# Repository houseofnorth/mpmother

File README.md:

# MPMOTHER

House of North 2026

| Knob | Name     | MIDI Out (default) | MIDI In (default) |
|------|----------|--------------------|-------------------|
| 1    | SPACE    | ch 1, CC 20        | ch 2, CC 20       |
| 2    | TEXTURE  | ch 1, CC 21        | ch 2, CC 21       |
| 3    | MOVEMENT | ch 1, CC 22        | ch 2, CC 22       |
| 4    | SHADOW   | ch 1, CC 23        | ch 2, CC 23       |

MIDI Out is what a knob sends, MIDI In is what moves it. Every knob has its own channel and CC
for both, set in the config tool.

## Using it with Ableton Live

- **Map a knob:** MIDI-map a parameter to the knob as usual.
- **Knobs follow the set:** in Live's MIDI preferences, turn on *Remote* for the MPMOTHER
  **output**. Live then sends mapping feedback and the knobs jump to the right place.
- **Let Ableton drive the knobs:** send ch 2, CC 20–23 to MPMOTHER from a MIDI track
  (clips, automation, Max for Live LFOs). The knobs move and send their position, so whatever
  is mapped to them follows.
- A hand on a knob always wins.
- **Without motors:** Settings → *Motors* Off makes MPMOTHER a plain controller: the knobs only
  send, MIDI In is ignored.

## Config tool

Open <https://houseofnorth.github.io/mpmother/> in Chrome or Edge with the controller plugged in.
The first time, Chrome asks for permission to use MIDI devices: click **Allow**, the page needs it.
The main page shows the four knobs live (position, where the motor is heading, hand on knob).
**Settings** (top right) has all settings, calibration, wiper readings and faults.
It works while Ableton is running.

**As an app, offline:** click **Install** (top right; or the install icon in Chrome's address bar).
MPMOTHER then opens in its own window from the Dock / Start menu and works without internet.
It updates itself whenever it is opened online.

**Demo** (top right): with the controller connected, the knobs make random moves until you
press Demo again. Without a controller it shows a simulated one.

## Status LED

| Colour          | Meaning |
|-----------------|---------|
| dim green       | ready |
| blue flicker    | MIDI in or out |
| red blink       | fault, motors held off |
| solid red       | driver kept faulting, needs *Clear faults* or a power cycle |
| white blink ×3  | restarted by the watchdog |

## Hardware

A main board (MPMOTHER v1) and one pot board (MPCHILD v1) per knob. Schematic, board file,
Gerbers and pictures: [hardware/](hardware/).

## Firmware

PlatformIO project. Open this folder in VS Code with the PlatformIO extension, then
*Build* (✓) and *Upload* (→). Serial monitor at 115200 – type `help` for text commands.

First time on new hardware: run **Calibrate** (config tool or `calibrate`), hands off the knobs.

Code layout and tuning values are explained at the top of each file in `src/`.
SysEx details: [PROTOCOL.md](PROTOCOL.md).

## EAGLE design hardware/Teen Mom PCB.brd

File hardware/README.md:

# Hardware

Schematics and board files for MPMOTHER v1, designed in Fusion Electronics.

| Board | What it is |
|-------|------------|
| MPMOTHER v1 | Main board: Teensy 4.1, two Pololu DRV8833 drivers, four IDC 2×4 headers to the pot boards |
| MPCHILD v1  | Pot board, one per knob: the motorised pot and its IDC 2×4 header |

## Files

| File | What it is |
|------|------------|
| [`Teensy_Mother_Schematic.sch`](Teensy_Mother_Schematic.sch) | MPMOTHER v1 schematic (EAGLE format, from Fusion Electronics) |
| [`Teen Mom PCB.brd`](Teen%20Mom%20PCB.brd) | MPMOTHER v1 board layout (EAGLE format, "Teen Mom PCB" in Fusion) |
| [`gerbers/Teen_Mom_PCB_Manufacturing_Output.zip`](gerbers/Teen_Mom_PCB_Manufacturing_Output.zip) | MPMOTHER v1 manufacturing output: Gerbers, drill, pick and place, parts list |
| [`gerbers/Motorboard_pcb_Manufacturing_Output.zip`](gerbers/Motorboard_pcb_Manufacturing_Output.zip) | MPCHILD v1 manufacturing output: Gerbers, drill, pick and place |

The Gerber zips are the v1 boards as ordered (JLCPCB): upload a zip as it is.
Pin map and wiring as used by the firmware: [`src/pins.h`](../src/pins.h).

## MPMOTHER v1 (main board)

Layout:

Schematic:

## MPCHILD v1 (pot board)

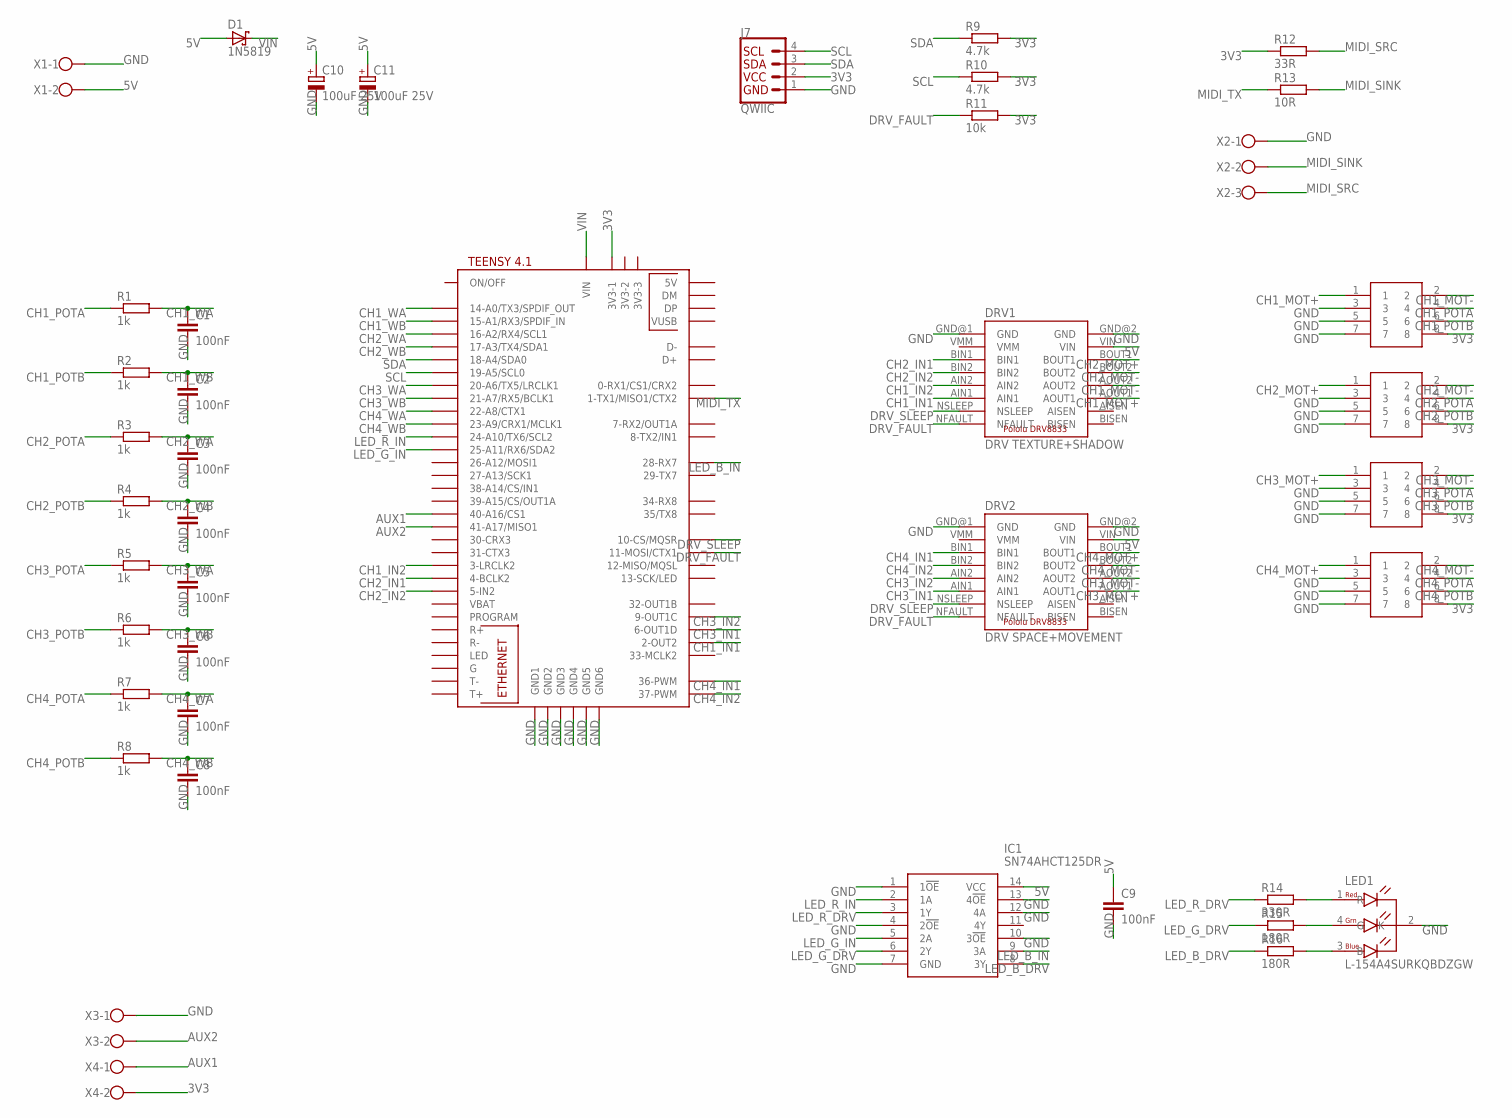
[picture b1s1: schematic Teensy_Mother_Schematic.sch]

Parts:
C1, C2, C3, C4, C5, C6, C7, C8, C9: 100nF; C050-025X075
C10, C11: 100uF 25V; E3,5-8
D1: 1N5819; DO41-10
DRV1: DRV TEXTURE+SHADOW; POLOLU_2130_FH
DRV2: DRV SPACE+MOVEMENT; POLOLU_2130_FH
IC1: SN74AHCT125DR; SOIC127P600X175-14N
J1: SHADOW; BOXHDR_2X4_V
J2: TEXTURE; BOXHDR_2X4_V
J3: MOVEMENT; BOXHDR_2X4_V
J4: SPACE; BOXHDR_2X4_V
J7: QWIIC; 1X04
LED1: L-154A4SURKQBDZGW; LED5MM_RGB_4L_STAGGER
R1, R2, R3, R4, R5, R6, R7, R8: 1k; 0204/7
R9, R10: 4.7k; 0204/7
R11: 10k; 0204/7
R12: 33R; 0204/7
R13: 10R; 0204/7
R14: 330R; 0204/7
R15, R16: 180R; 0204/7
U$1: TEENSY41
X1, X3, X4: W237-1023D; W237-102
X2: W237-103

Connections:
3V3: J1.8, J2.8, J3.8, J4.8, J7.2, R9.2, R10.2, R11.2, R12.1, U$1.3V3-1, X4.2
5V: C9.1, C10.+, C11.+, D1.A, DRV1.VIN, DRV2.VIN, IC1.14 (VCC), X1.2
AUX1: U$1.40-A16/CS1, X4.1
AUX2: U$1.41-A17/MISO1, X3.2
CH1_IN1: DRV1.AIN1, U$1.2-OUT2
CH1_IN2: DRV1.AIN2, U$1.3-LRCLK2
CH1_MOT+: DRV1.AOUT1, J1.1
CH1_MOT-: DRV1.AOUT2, J1.2
CH1_POTA: J1.4, R1.1
CH1_POTB: J1.6, R2.1
CH1_WA: C1.1, R1.2, U$1.14-A0/TX3/SPDIF_OUT
CH1_WB: C2.1, R2.2, U$1.15-A1/RX3/SPDIF_IN
CH2_IN1: DRV1.BIN1, U$1.4-BCLK2
CH2_IN2: DRV1.BIN2, U$1.5-IN2
CH2_MOT+: DRV1.BOUT1, J2.1
CH2_MOT-: DRV1.BOUT2, J2.2
CH2_POTA: J2.4, R3.1
CH2_POTB: J2.6, R4.1
CH2_WA: C3.1, R3.2, U$1.16-A2/RX4/SCL1
CH2_WB: C4.1, R4.2, U$1.17-A3/TX4/SDA1
CH3_IN1: DRV2.AIN1, U$1.6-OUT1D
CH3_IN2: DRV2.AIN2, U$1.9-OUT1C
CH3_MOT+: DRV2.AOUT1, J3.1
CH3_MOT-: DRV2.AOUT2, J3.2
CH3_POTA: J3.4, R5.1
CH3_POTB: J3.6, R6.1
CH3_WA: C5.1, R5.2, U$1.20-A6/TX5/LRCLK1
CH3_WB: C6.1, R6.2, U$1.21-A7/RX5/BCLK1
CH4_IN1: DRV2.BIN1, U$1.36-PWM
CH4_IN2: DRV2.BIN2, U$1.37-PWM
CH4_MOT+: DRV2.BOUT1, J4.1
CH4_MOT-: DRV2.BOUT2, J4.2
CH4_POTA: J4.4, R7.1
CH4_POTB: J4.6, R8.1
CH4_WA: C7.1, R7.2, U$1.22-A8/CTX1
CH4_WB: C8.1, R8.2, U$1.23-A9/CRX1/MCLK1
DRV_FAULT: DRV1.NFAULT, DRV2.NFAULT, R11.1, U$1.11-MOSI/CTX1
DRV_SLEEP: DRV1.NSLEEP, DRV2.NSLEEP, U$1.10-CS\MQSR (10-CS/MQSR)
GND: C1.2, C2.2, C3.2, C4.2, C5.2, C6.2, C7.2, C8.2, C9.2, C10.-, C11.-, DRV1.GND@1 (GND), DRV1.GND@2 (GND), DRV2.GND@1 (GND), DRV2.GND@2 (GND), IC1.1 (1!OE), IC1.4 (2!OE), IC1.7 (GND), IC1.10 (3!OE), IC1.12 (4A), IC1.13 (4!OE), J1.3, J1.5, J1.7, J2.3, J2.5, J2.7, J3.3, J3.5, J3.7, J4.3, J4.5, J4.7, J7.1, LED1.2 (K), U$1.GND1, U$1.GND2, U$1.GND3, U$1.GND4, U$1.GND5, U$1.GND6, X1.1, X2.1, X3.1
LED_B: LED1.3 (B), R16.2
LED_B_DRV: IC1.8 (3Y), R16.1
LED_B_IN: IC1.9 (3A), U$1.28-RX7
LED_G: LED1.4 (G), R15.2
LED_G_DRV: IC1.6 (2Y), R15.1
LED_G_IN: IC1.5 (2A), U$1.25-A11/RX6/SDA2
LED_R: LED1.1 (R), R14.2
LED_R_DRV: IC1.3 (1Y), R14.1
LED_R_IN: IC1.2 (1A), U$1.24-A10/TX6/SCL2
MIDI_SINK: R13.2, X2.2
MIDI_SRC: R12.2, X2.3
MIDI_TX: R13.1, U$1.1-TX1/MISO1/CTX2
SCL: J7.4, R10.1, U$1.19-A5/SCL0
SDA: J7.3, R9.1, U$1.18-A4/SDA0
VIN: D1.C, U$1.VIN

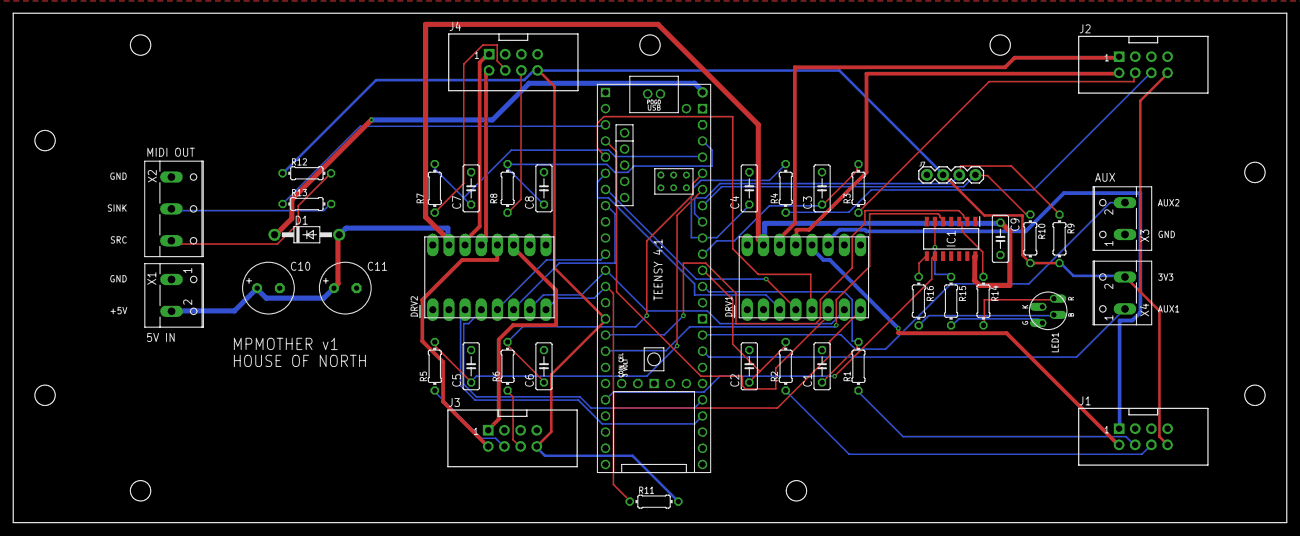
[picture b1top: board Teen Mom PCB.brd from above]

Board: 2 copper layers, 200.0 x 80.0 mm, 42 parts (0 on the bottom side), 54 nets.

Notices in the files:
parts and their libraries:
Qwiic4: Licensing: Creative Commons ShareAlike 4.0 International - https://creativecommons.org/licenses/by-sa/4.0
